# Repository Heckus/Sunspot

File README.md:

#  3D Volleyball Tracker with ROS2 

This repository contains the source code for a real-time 3D volleyball tracking system developed for a Raspberry Pi. The system uses a camera, a custom AI model, and the **Robot Operating System 2 (ROS2)** to detect a volleyball and determine its precise 3D position.

This project serves as a comprehensive demonstration of skills in **robotics**, **AI**, and **computer vision**, from low-level hardware communication to high-level software architecture.

---

##  Overview

The core objective of this project is to create a robust and scalable system that can:

-   Capture a live video stream from a camera connected to a Raspberry Pi.
-   Detect a volleyball in the video feed using a custom-trained **YOLO** object detection model.
-   Calculate the **3D coordinates (x, y, z)** of the detected volleyball using camera calibration data.
-   Publish the 3D position and other relevant data as **ROS2 topics**, allowing for seamless integration with other robotic systems.

---

##  Key Features

-   **Real-time Performance**: Optimized for high-speed processing on a Raspberry Pi.
-   **AI-Powered Detection**: Utilizes a custom-trained **YOLOv5** model for accurate and efficient volleyball detection.
-   **3D Position Estimation**: Implements computer vision techniques to translate 2D image coordinates into real-world 3D positions.
-   **Modular ROS2 Architecture**: Built with a modular node-based structure in ROS2, allowing for easy testing, debugging, and expansion.
-   **Calibration Utilities**: Includes dedicated ROS2 nodes for performing extrinsic camera calibration.
-   **System Monitoring**: Features a battery monitoring node to track the robot's power status.
-   **Visualization Ready**: Comes with RViz configuration files for easy visualization of the robot model and sensor data.

---

##  Tech Stack & Skills Demonstrated

This project showcases a wide range of in-demand skills in robotics and software engineering:

-   **Programming**: Advanced proficiency in **Python** for developing complex, multi-node robotic systems.
-   **Robotics**:
    -   **ROS2**: Deep understanding of the ROS2 framework, including creating nodes, topics, services, launch files, and URDF models.
    -   **System Integration**: Expertise in integrating various hardware and software components into a cohesive robotic system.
    -   **TF2 (Transformations)**: Using the TF2 library to manage and broadcast coordinate frame transformations within ROS2.
-   **Computer Vision**:
    -   **OpenCV**: Extensive use of OpenCV for image processing, camera interfacing, and calibration.
    -   **Camera Calibration**: Practical application of camera calibration techniques to solve for intrinsic and extrinsic parameters.
-   **Artificial Intelligence**:
    -   **Object Detection**: Experience training and deploying custom object detection models (YOLO).
    -   **PyTorch**: Integrating PyTorch-based models into a real-time application.
-   **Hardware & Embedded Systems**:
    -   **Raspberry Pi**: Setting up and developing for a Raspberry Pi in a robotics context.
    -   **Sensor Interfacing**: Interfacing with cameras and system-level utilities (e.g., battery monitoring).

---

##  System Architecture

The system is composed of several key ROS2 nodes that work in concert:

-   `camera_node`: Captures images from the camera and publishes them to a topic.
-   `detection_node`: Subscribes to the image topic, runs the YOLO model to detect the volleyball, and publishes the 2D bounding box coordinates.
-   `calculation_node`: Subscribes to the detection results and uses calibration data to calculate and publish the 3D position of the volleyball.
-   `extrinsic_calibration_node`: A utility node to help perform and save the camera's extrinsic calibration.
-   `battery_monitor_node`: A utility node that periodically checks and publishes the device's battery status.

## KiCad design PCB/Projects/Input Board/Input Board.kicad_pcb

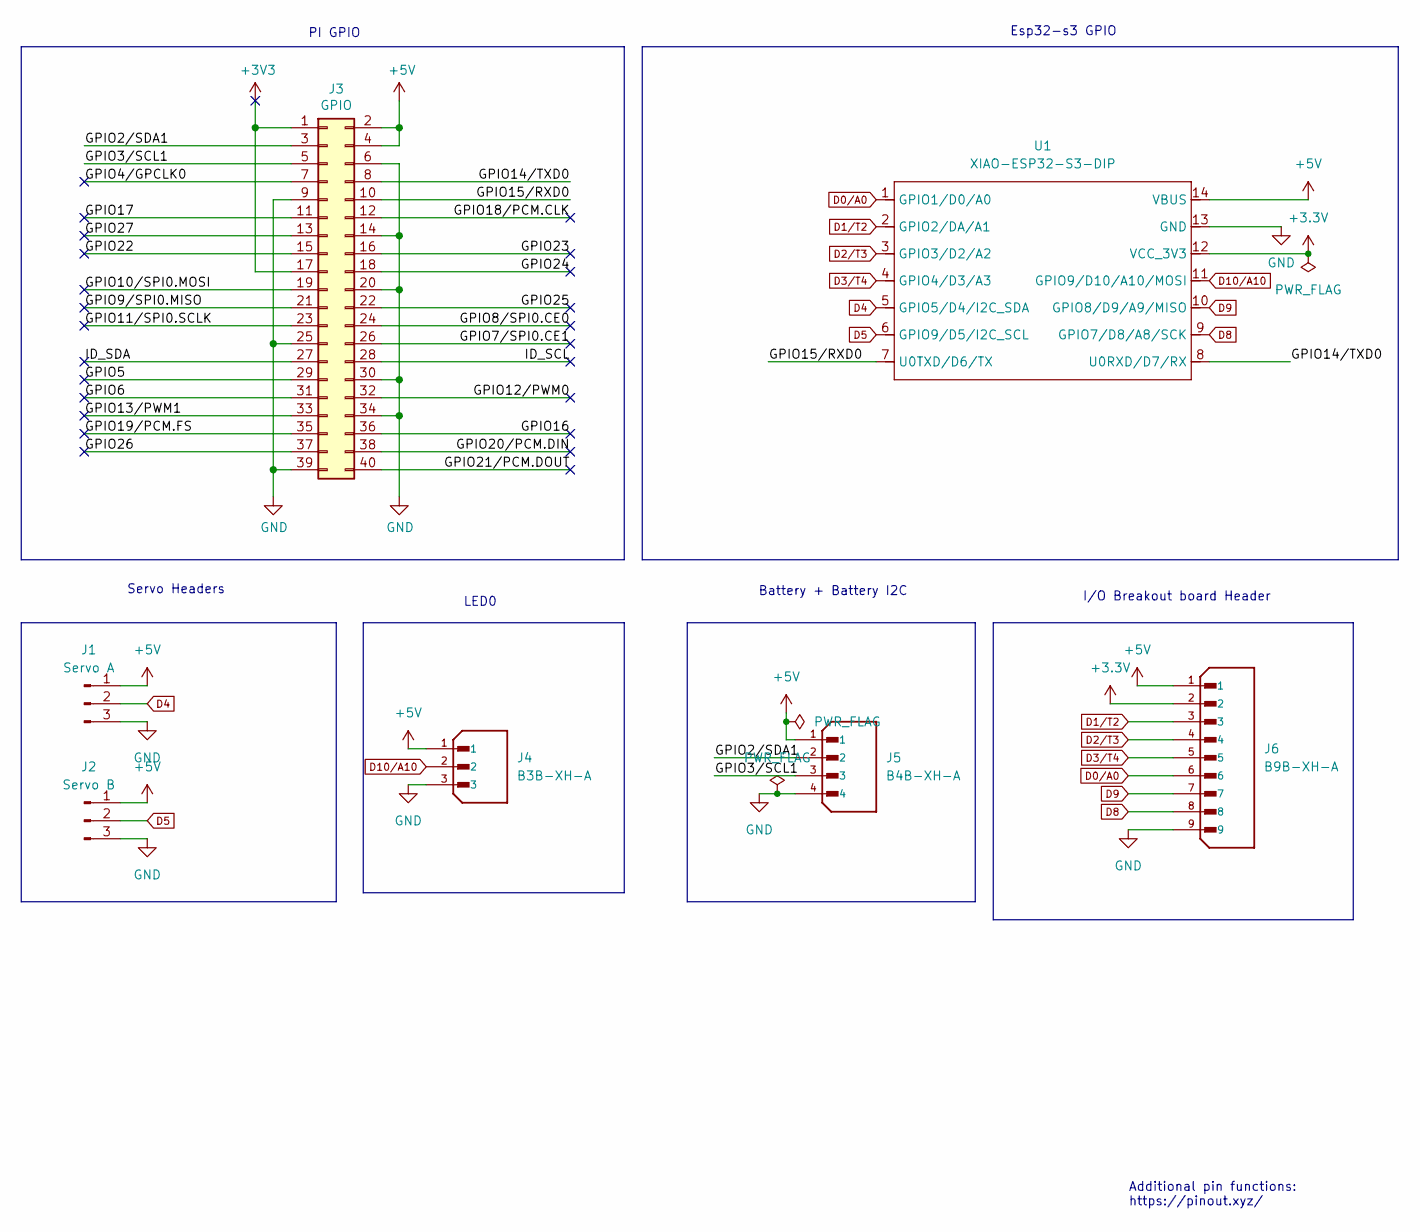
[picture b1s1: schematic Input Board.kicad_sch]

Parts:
J1: Servo A; PinHeader_1x03_P2.54mm_Vertical
J2: Servo B; PinHeader_1x03_P2.54mm_Vertical
J3: GPIO; PinSocket_2x20_P2.54mm_Vertical
J4: B3B-XH-A; JST_XH_B3B-XH-A_1x03_P2.50mm_Vertical; PARTREV 7/4/21
J5: B4B-XH-A; JST_XH_B4B-XH-A_1x04_P2.50mm_Vertical; PARTREV 7/4/21
J6: B9B-XH-A; JST_XH_B9B-XH-A_1x09_P2.50mm_Vertical; PARTREV 7/4/21
U1: XIAO-ESP32-S3-DIP; XIAO-ESP32S3-DIP

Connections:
+3.3V: J6.2, U1.12 (VCC_3V3)
+3V3: J3.1, J3.17
+5V: J1.1, J2.1, J3.2, J3.4, J4.1, J5.1, J6.1, U1.14 (VBUS)
/GPIO2/SDA1: J3.3, J5.2
/GPIO3/SCL1: J3.5, J5.3
/GPIO4/GPCLK0: J3.7
/GPIO5: J3.29
/GPIO6: J3.31
/GPIO7/SPI0.CE1: J3.26
/GPIO8/SPI0.CE0: J3.24
/GPIO9/SPI0.MISO: J3.21
/GPIO10/SPI0.MOSI: J3.19
/GPIO11/SPI0.SCLK: J3.23
/GPIO12/PWM0: J3.32
/GPIO13/PWM1: J3.33
/GPIO14/TXD0: J3.8, U1.8 (U0RXD/D7/RX)
/GPIO15/RXD0: J3.10, U1.7 (U0TXD/D6/TX)
/GPIO16: J3.36
/GPIO17: J3.11
/GPIO18/PCM.CLK: J3.12
/GPIO19/PCM.FS: J3.35
/GPIO20/PCM.DIN: J3.38
/GPIO21/PCM.DOUT: J3.40
/GPIO22: J3.15
/GPIO23: J3.16
/GPIO24: J3.18
/GPIO25: J3.22
/GPIO26: J3.37
/GPIO27: J3.13
/ID_SCL: J3.28
/ID_SDA: J3.27
D0/A0: J6.6, U1.1 (GPIO1/D0/A0)
D1/T2: J6.3, U1.2 (GPIO2/DA/A1)
D2/T3: J6.4, U1.3 (GPIO3/D2/A2)
D3/T4: J6.5, U1.4 (GPIO4/D3/A3)
D4: J1.2, U1.5 (GPIO5/D4/I2C_SDA)
D5: J2.2, U1.6 (GPIO9/D5/I2C_SCL)
D8: J6.8, U1.9 (GPIO7/D8/A8/SCK)
D9: J6.7, U1.10 (GPIO8/D9/A9/MISO)
D10/A10: J4.2, U1.11 (GPIO9/D10/A10/MOSI)
GND: J1.3, J2.3, J3.6, J3.9, J3.14, J3.20, J3.25, J3.30, J3.34, J3.39, J4.3, J5.4, J6.9, U1.13 (GND)

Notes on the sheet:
PI GPIO
Battery + Battery I2C
Servo Headers
Additional pin functions: https://pinout.xyz/
LED0
I/O Breakout board Header
Esp32-s3 GPIO

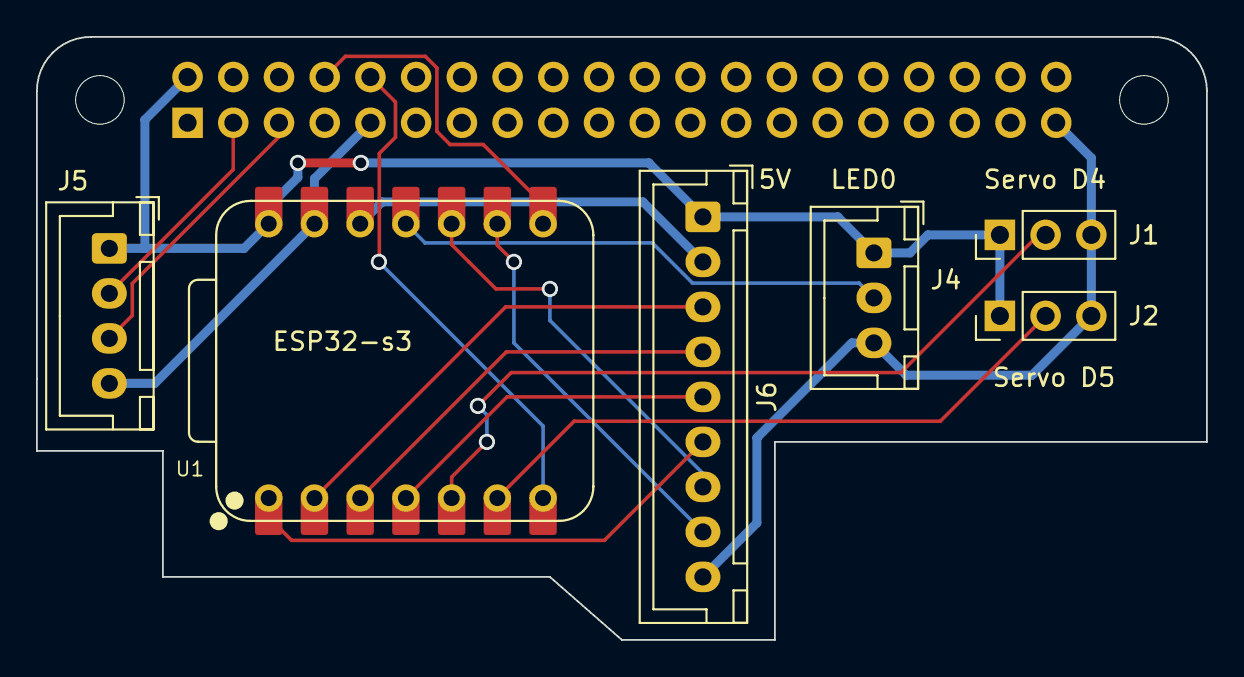
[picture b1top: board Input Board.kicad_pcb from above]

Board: 2 copper layers, 65.0 x 33.5 mm, 9 parts (1 on the bottom side), 17 nets.

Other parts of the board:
MH1, MH2: MountingHole_2.7mm_M2.5

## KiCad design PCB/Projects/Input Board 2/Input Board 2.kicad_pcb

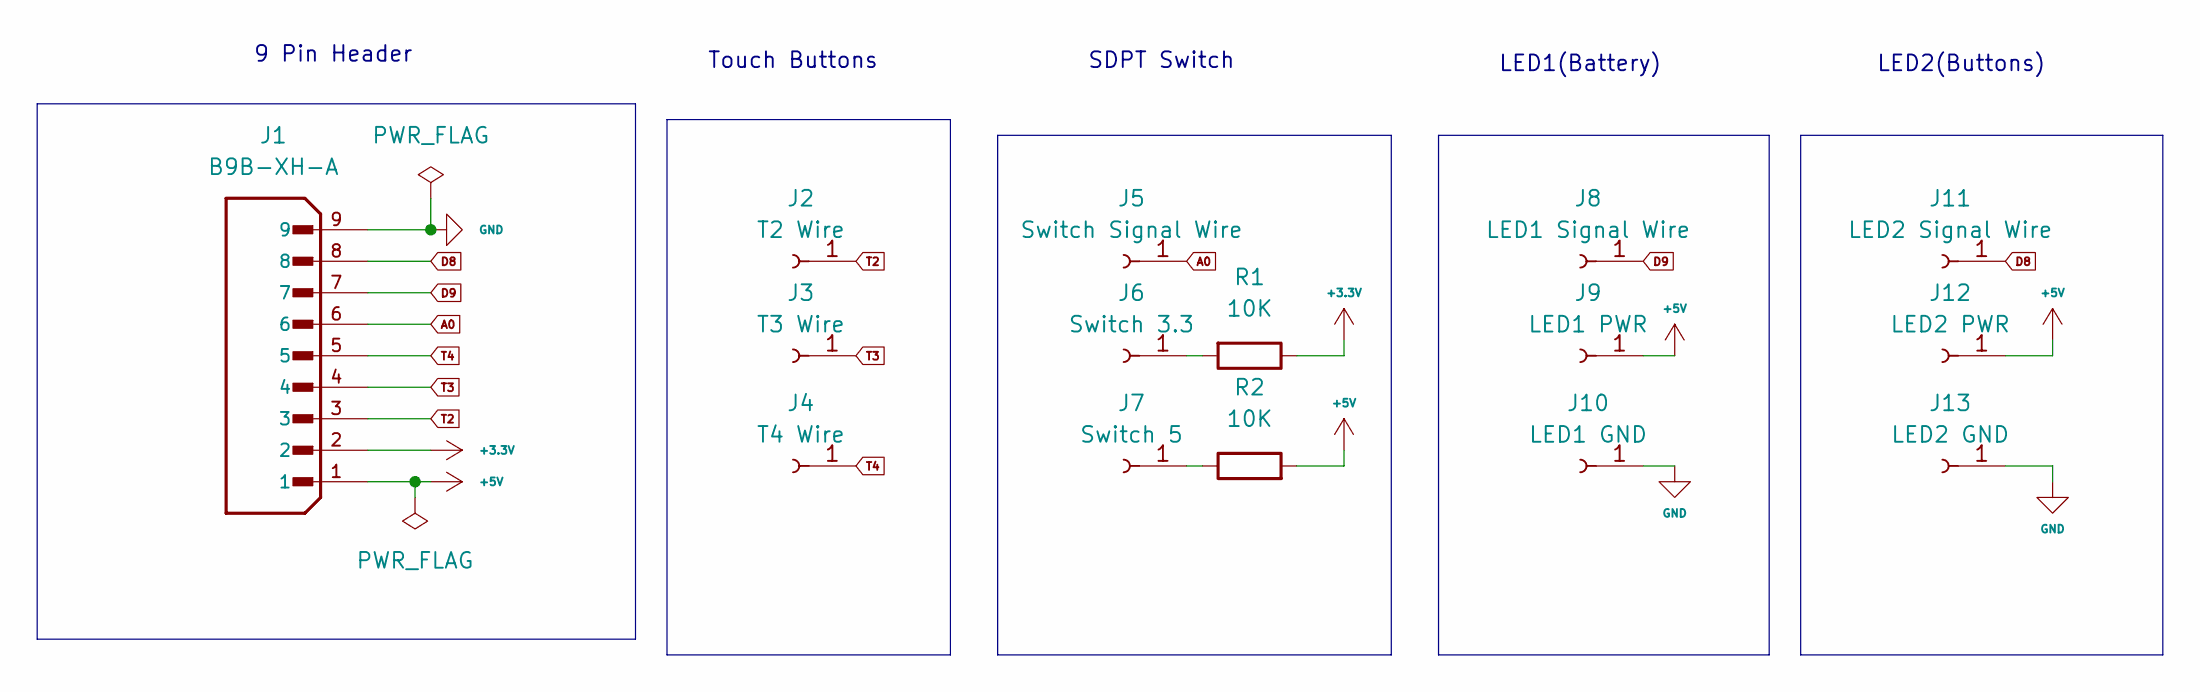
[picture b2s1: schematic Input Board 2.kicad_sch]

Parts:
J1: B9B-XH-A; JST_XH_B9B-XH-A_1x09_P2.50mm_Vertical; PARTREV 7/4/21
J2: T2 Wire; PinHeader_1x01_P2.54mm_Vertical
J3: T3 Wire; PinHeader_1x01_P2.54mm_Vertical
J4: T4 Wire; PinHeader_1x01_P2.54mm_Vertical
J5: Switch Signal Wire; PinHeader_1x01_P2.54mm_Vertical
J6: Switch 3.3; PinHeader_1x01_P2.54mm_Vertical
J7: Switch 5; PinHeader_1x01_P2.54mm_Vertical
J8: LED1 Signal Wire; PinHeader_1x01_P2.54mm_Vertical
J9: LED1 PWR; PinHeader_1x01_P2.54mm_Vertical
J10: LED1 GND; PinHeader_1x01_P2.54mm_Vertical
J11: LED2 Signal Wire; PinHeader_1x01_P2.54mm_Vertical
J12: LED2 PWR; PinHeader_1x01_P2.54mm_Vertical
J13: LED2 GND; PinHeader_1x01_P2.54mm_Vertical
R1, R2: 10K; R_Axial_DIN0309_L9.0mm_D3.2mm_P15.24mm_Horizontal

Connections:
+3.3V: J1.2, R1.1
+5V: J1.1, J9.1, J12.1, R2.2
A0: J1.6, J5.1
D8: J1.8, J11.1
D9: J1.7, J8.1
GND: J1.9, J10.1, J13.1
unnamed: J6.1, R1.2
unnamed: J7.1, R2.1
T2: J1.3, J2.1
T3: J1.4, J3.1
T4: J1.5, J4.1

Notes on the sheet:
LED1(Battery)
Touch Buttons
9 Pin Header
SDPT Switch
LED2(Buttons)

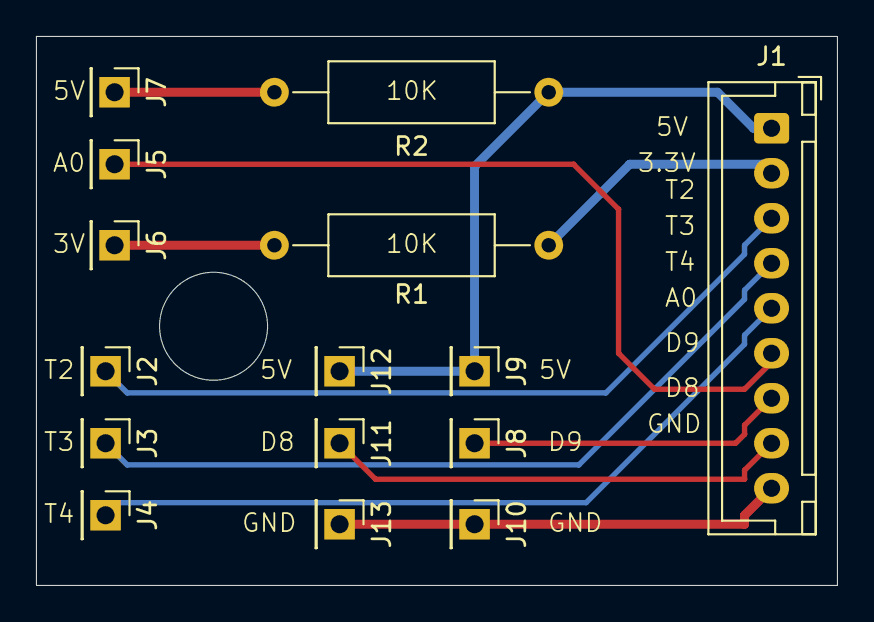
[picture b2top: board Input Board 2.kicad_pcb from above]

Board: 2 copper layers, 44.5 x 30.5 mm, 15 parts (0 on the bottom side), 11 nets.

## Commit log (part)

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2024-12-02 made progress on models for ball tracking
2024-12-04 4/10 vision model cascade4
2024-12-04 got imx219 working using a gstream pipeline on vision2. quaility os hot garbage but its a start
2024-12-04 trying to do manual preproccess work on imx219 camera
2024-12-05 trying to invesigate another method of accessing camera stream
2024-12-09 made some progress on saving and applying methods to streams. the saved videos are sped up, most likly due to gstream pipeline errors. cascade7 took 9.5 hours and so far had best training data but sh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
2024-12-10 missing battery voltage divider reading, finalised serial communication method and intergration of all components on main.cpp. So far all componenets have worked on arduino seperatly
2024-12-11 progress on microcontroller control and interfacing. missing batteryreader and regular button testing
2024-12-19 need to fix fast led library on esp32 port. untested as code cannot build
2024-12-20 stuck on esp32 code for serial for now, had led working but not intergrated with class code. their is some type of issue with pin definitions maybe
2024-12-21 got simple serial to work but my class version is not working
2024-12-21 the 3 way switch needs to be calibrated and the 3 tocuh buttons need proper deboucing but so far so good. had trouble with broken boot button on esp32 but fixed it
2024-12-22 small bug fixes needed like button and switch debouncing, maybe some error checking with serial depending on how good the defualt functions are. However ready to move to the design phase for circuit 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
2024-12-24 Update Claude-Waveshare UPS S3 Battery Monitoring in C++.md
    added code
2024-12-27 Added comps for pcb
2024-12-27 Circuit boards done, send for manufacture
2024-12-30 added working code to notes
2024-12-31 im doing this on new years fml
2025-01-01 oop os
2025-01-01 switching to pi as my vs on pc is saying my code is perfect... . Added more to threads
2025-01-01 fixed all issues on pi
2025-01-01 trying to remove microcontrollers
2025-01-01 Cmake works]
2025-01-21 on my pc now
2025-02-03 so far servos and LED0 work as intended, need to test buttons, switch and led1+2. Concerns about current draw as there is 3.7A for the whole device, pi takes 3 leaving .7 for 12 leds+2servos+100milia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
2025-02-03 switch is broken rn, need to test full intergration and ensure buttons dont play up and leds dont play up. going to test operation with pi being powered as well(not looking good)
2025-02-04 desktopchanges
2025-02-04 cleaned and read to test
2025-02-04 added untested chnages, added ui
2025-02-04 code gets to thread point then pi dies, cause unknown (mostlikly power draw from led+servo). dont want to break pi so a couple more tests then stop
2025-02-07 added vscode
2025-02-07 refactoring
2025-02-09 servo fix + remove deboucing
2025-02-09 Updates to main
2025-02-09 changes to main. i have a queue access error that occurs but currently unable to narrow down what uses the std::queue not safely(probs all of it is ai code)
2025-02-09 changes to line 24 in main
2025-02-09 changes to print as boxes dont work on terminal without extra lib
2025-02-09 fixes to monitoring
2025-02-09 fixes to monitoring time
2025-02-09 fix to write time to stop the recorded video from being sped up
2025-02-09 camera is private, removing extra check
2025-02-10 changes to main tracking, main mc start up and tools print statement
2025-02-11 small changes
2025-02-11 differnet approach to combat queue issues. defined a queue to share frames between threads instead. i dont know if this will fix the cause ot jsut add more complexity. Going to look into cause more i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
2025-02-11 added queue class
2025-02-11 now we send the angle we want, the change is calculated and stored on pi
2025-03-31 lite added
2025-03-31 gpio change
2025-03-31 Update check_ip.py
    added use link
2025-04-01 camera method change on recording2
2025-04-01 stream fixes and added button to start recording(getting around lack of working switch)
2025-04-01 battery addition
2025-04-01 battery addition changes for
2025-04-01 sync
2025-04-01 noir approach
2025-04-01 fix file corrupt and added toggle script
2025-04-01 removed space
2025-04-01 added reset button
2025-04-01 fix to hmtl
2025-04-01 7# changes
2025-04-01 rename toggle
2025-04-01 thread shutdown timing causeing reboot bug fix
2025-04-02 changes to methods in toggle.sh and recording8(8 is a test move to 7 when confirmed)
2025-04-02 lite code works now with toggle turning the AP and python scrip on on start up, then once connected the shutdown button returns the pi to normal use
2025-04-08 this is the start of a rework. the 4k now lags which means a previous iteration worked better so i need to find it. Also the toggle sh script doesnt turn internet AP on so that needs to be fixed aswe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
2025-04-08 first attempt at fix, jpeg 85->75 and changed toggle script
2025-04-09 the toggle script was not turning service disable off and the AP would disappear after restart
2025-04-09 made changes to the python script to ensure it calls the toggle script when the shutdown button is clicked on ui
2025-04-10 syntax error with AWB update new version
2025-04-10 syntax error with AWB update new version, removed noisereduction for now
2025-04-10 fully moved to full settings control approach, untested yet def has bugs
2025-04-10 fully moved to full settings control approach, untested yet def has bugs. added draft to line 1410
2025-04-10 works but there is isssues with resolution chnage and bugged ui
2025-04-10 pivot to ui debugg logging changed to info
2025-04-10 index route changes
2025-04-10 index route changes, this is working now
2025-04-10 issue with index, this is attempt 1
2025-04-10 issue with index, this is attempt 2
2025-04-14 added servo test. if pi cannot run with servo drawing from same power source in this test need different servo or secondary ps
2025-04-14 changed to hardware pwm and also added ctrl c catch
2025-04-14 pigpiod doesnt exist, switching to lgpio
2025-04-14 trying a hardware method on servo2, added channel 0
2025-04-14 servo3 is a stripped down moduled that is ready to use in sunspot for single servo control
2025-04-14 servo3 fixes
2025-04-14 added pinout
2025-04-15 this is the orignal solution before changes, untested
2025-04-15 added a virtual environmnet to get required packages
2025-04-15 libcamera fix attempt 1
2025-04-15 new venv with different flags
2025-04-15 added libs
2025-04-15 venv created on pi
2025-04-15 added test
2025-04-15 working on pi, now time to debug
2025-04-15 went back to libcamera import as its correct
2025-04-15 i had the switch the wrong way round gg
2025-04-15 recording has bugs, applied 2 fixes
2025-04-15 recording now only is sped up, changes to main loop to try and sync fps to write speed
2025-04-15 added print to check if fps is bursting
2025-04-15 fps fix in camera_manager
2025-04-15 camera_manager with debug logging
2025-04-15 camera_manager with debug logging, fixing debug
2025-04-15 SYNCED
2025-04-16 attempt 2 at fix, changes to config
2025-04-16 attempt 3, debug working now
2025-04-16 attempt 4, debug lines in info
2025-04-16 attempt 5, changes to audio encoding
2025-04-16 attempt 5, trying to boost power by removing cam1 with toggle
2025-04-16 attempt 7, audio issue + chnages to fps
2025-04-16 attempt 7, fps change
2025-04-16 attempt 7, fps change 30
2025-04-16 pivot to refactor
2025-04-16 audio out of sync, adjsuting audio_start_offset to tune
2025-04-16 working iteration, saved to old2
2025-04-16 smoothing on servo movement
2025-04-16 iso change on ui
2025-04-25 new camera saving method
2025-04-25 servo fix in config
2025-04-25 usb is bottle neck for recording, which is casuing recording to speed up
2025-04-25 revert change, going to try ssd approach
2025-04-25 20 fps
2025-04-25 audio sync fix
2025-04-25 audio sync fix 2
2025-04-25 audio sync fix 3
2025-04-25 audio sync fix 5
2025-04-25 audio sync fix 6
2025-05-03 no audio pivot start
2025-05-03 removed audio,added multiprocess comments, added cv_functions
2025-05-03 calibration code
2025-05-03 all recordings are sped uo, refactored approach to try and solve
2025-05-03 changes to stop recording
2025-05-03 stop recording
2025-05-03 files cannot open
2025-05-03 files cannot open fix 2
2025-05-03 cv_testing
2025-05-03 meow lol, nah i removed config dependance from the computer vision stuff so the tests can run without pi packages
2025-05-03 need valid data to continue with succesful computer vision
2025-05-12 fix to liuke 269
2025-05-22 calibration change
2025-05-22 calibration change3
2025-05-22 calibration change4
2025-05-22 cameramanagerfix1
2025-05-23 colour fix again plus other fixes
2025-05-23 webui changes meow
2025-05-23 volleyball detection troubles
2025-05-23 volleyball detection troubles solved removing masks
2025-05-23 improvement to main
2025-05-23 webui buff2
2025-05-23 webui buff3
2025-05-23 webui buff4
2025-05-23 webui buff6
2025-05-23 webui buff7
2025-05-23 intrinsic recalibration
2025-05-24 intrinsic recalibration code add lmb
2025-05-24 new mapping technique
2025-06-23 remove files
2025-06-24 ready for training
2025-06-24 pi55
2025-06-24 more robust code
2025-06-24 more robust and flexible
2025-06-24 bothmodels now trained
2025-06-24 bothmodels now trained, new method for bbox
2025-06-24 added early stop
2025-06-25 detection phase
2025-06-25 new approach, tflite and additional filtering for ball and number detection
2025-06-26 ball detection upgrade
2025-06-26 ball detection upgrade, now toggleable
2025-06-26 new models
2025-06-27 folderchange
2025-06-27 training
2025-06-28 version2 work, i trained a n ball model lets test
2025-06-28 added all
2025-06-28 step in the right direction, we now have a model which is kind of good at identfying balls and now we get more data to improve it
2025-06-29 updated dataset creator
2025-06-30 added dataset manager tool as i noticed that some of the annotations are wrong and 1000 images are being considered background for some reason
2025-06-30 trying to make a webapp to help with dataset management(my current dataset has alot of bad images in it that swhy training sucks)
2025-06-30 changes to ros md
2025-07-03 made yolo tool useable
2025-07-05 yolo in extrinsic
2025-07-05 updated read me
2025-07-05 0.952 0.912
2025-07-06 training for ball 4 cut short, not sig change after epoch60. look into way to cut training short properly, as ctrl c does not produce any metrics.
2025-07-06 added stop if no improvement for x epochs argument for trainer
2025-07-06 new detection model on ExIn
2025-07-06 webui broken, trying to fix
2025-07-07 ros2_ws made, testing now
2025-07-11 raw docker approach, distrobox not working
2025-07-14 dockerfile
2025-07-14 setup+model
2025-07-14 dockerfile update (probs wont work)
2025-07-14 dockerfile update, both compile now just need to test this one
2025-07-14 different docker approach,built ros2 from source
2025-07-14 close to final docker solution
2025-07-14 polishing docker solution
2025-07-14 no clone at end
2025-07-14 keys
2025-07-15 main refactoring
2025-07-15 saving dockerfile
2025-07-15 PV1 complie
2025-07-16 ros2_ws work
2025-07-16 ros2_ws work models
2025-07-16 ros2_ws models test
2025-07-16 court updates
2025-07-16 court updates stl
2025-07-17 Dockerfile change, camera nodes cannot see the camera hardware in container, thinkings its a libcamera version issue
2025-07-17 new launch
2025-07-17 new docker again
2025-07-17 new docker
2025-07-17 new docker additions
2025-07-17 new docker libcamera flags v3
2025-07-17 dockerfile complied but colcon dont work, modifying docker file
2025-07-17 more changes, need to test
2025-07-18 modified permissions
2025-07-18 tests for picamera2
2025-07-18 tests for picamera2, dockerfile update so picamera2 works
2025-07-18 we are trying to complie picamera2 so we can make a custom node
2025-07-20 docker file sync
2025-07-20 added launch file and a cyclone dds
2025-07-20 trying new dockerfile
2025-07-21 main refactor before public
